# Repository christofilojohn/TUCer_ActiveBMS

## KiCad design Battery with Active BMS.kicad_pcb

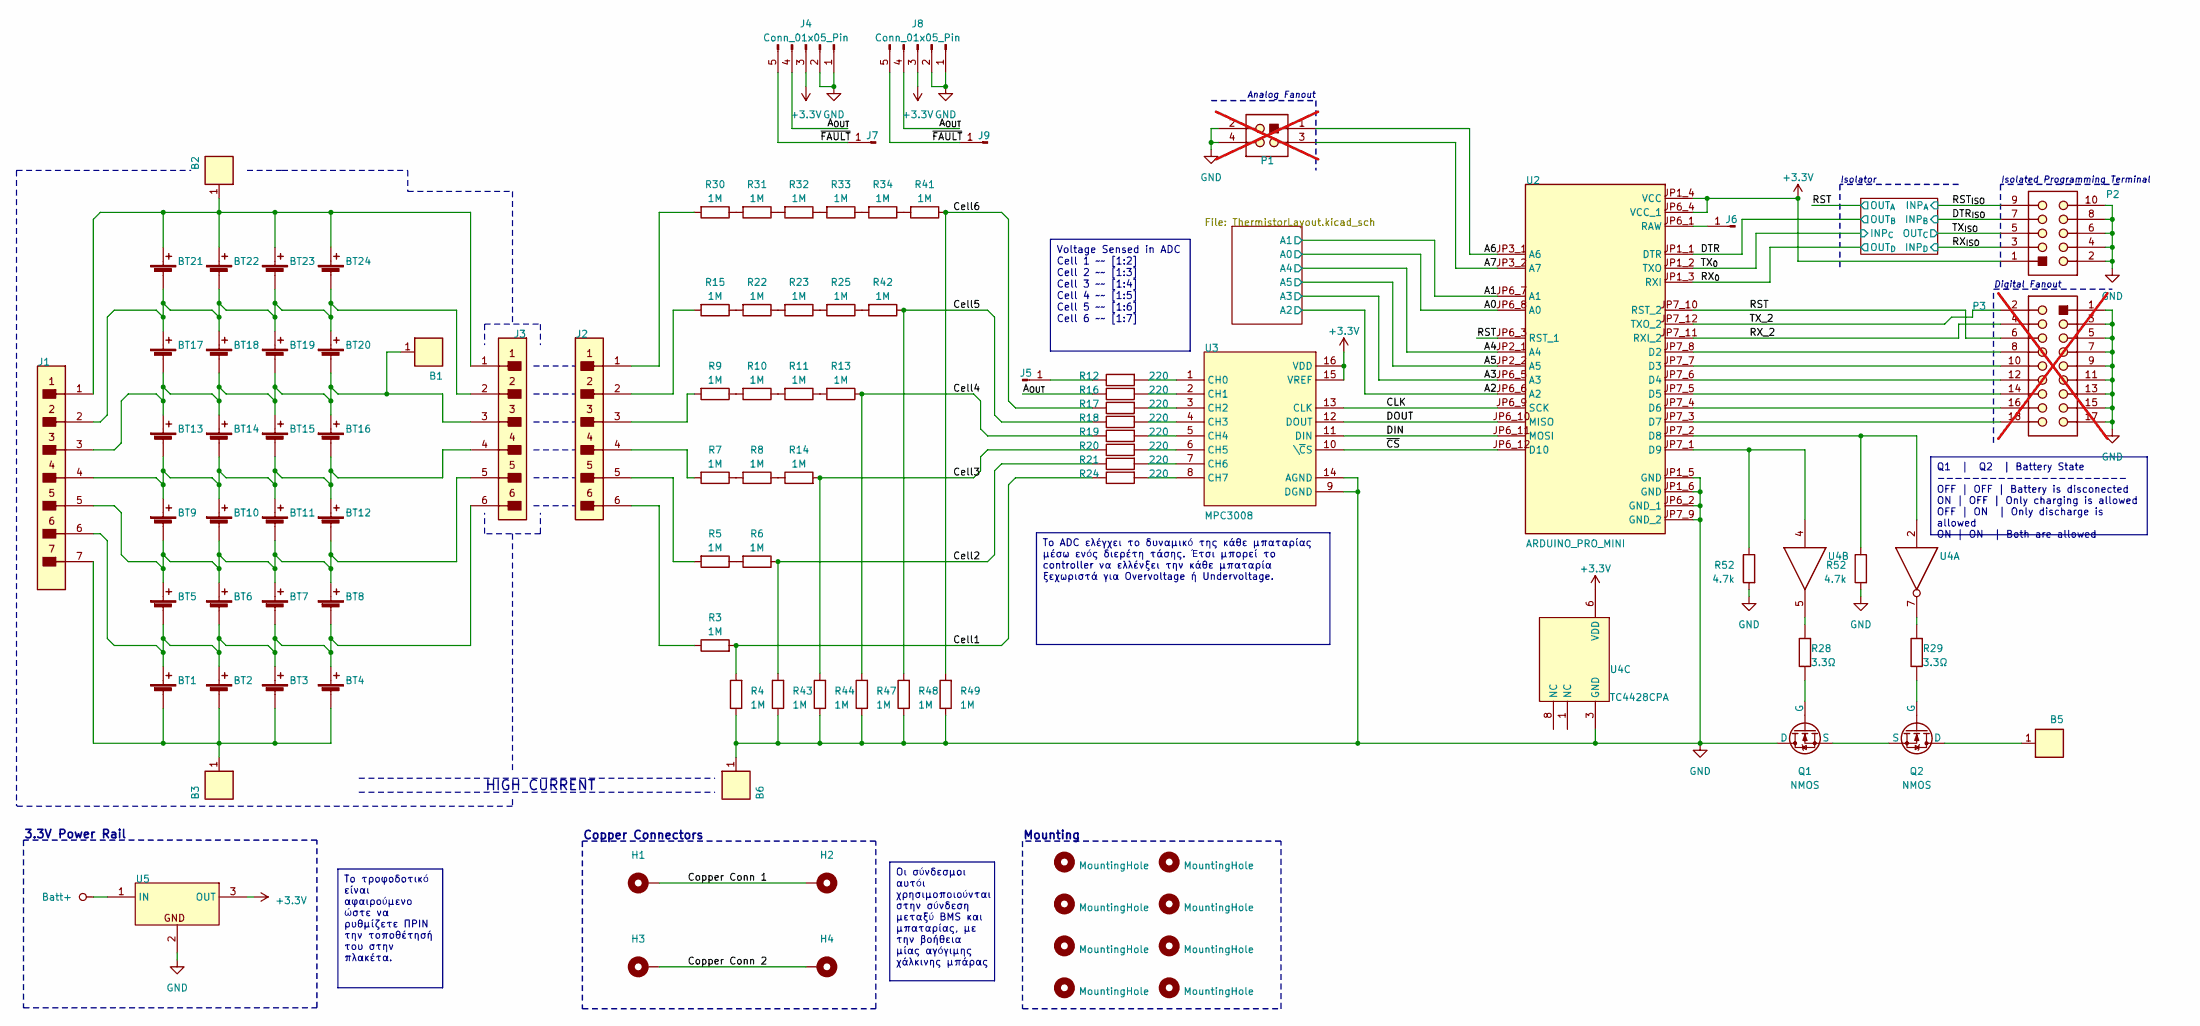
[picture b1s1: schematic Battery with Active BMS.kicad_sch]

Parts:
B1, B2, B3, B5, B6: 7461383; M5 Screw Terminal; MOUSER PART NUMBER 710-7461383
BT1, BT2, BT3, BT4, BT5, BT6, BT7, BT8, BT9, BT10, BT11, BT12, BT13, BT14, BT15, BT16, BT17, BT18, BT19, BT20, BT21, BT22, BT23, BT24: Battery_Cell; 21700
H1, H2, H3, H4: MountingHole_Pad; MountingHole_5.3mm_M5_Pad_Via
H5, H6, H7, H8, H9, H10, H11, H12: MountingHole; MountingHole_2.5mm_Pad
J1: B7B-EH-A(LF)(SN); JST_EH_B7B-EH-A_1x07_P2.50mm_Vertical; FLAMMABILITY RATING UL94 V-0; CURRENT RATING 3A
J2, J3: B7B-EH-A(LF)(SN); JST_EH_B6B-EH-A_1x06_P2.50mm_Vertical; FLAMMABILITY RATING UL94 V-0; CURRENT RATING 3A
J4, J8: Conn_01x05_Pin; PinSocket_1x05_P2.54mm_Vertical
J5, J6, J7, J9: Conn_01x01_Pin; PinSocket_1x01_P2.54mm_Vertical
P1: 22-28-4033; PinHeader_2x02_P2.54mm_Vertical; VOLTAGE RATING 250 V; CURRENT RATING 4 A; not fitted
P2: 61300511121; PinHeader_2x05_P2.54mm_Vertical; WORKING VOLTAGE 250VAC; WITHSTANDING VOLTAGE 500VAC; PART NUMBER 61300511121
P3: 61300811121; PinHeader_2x09_P2.54mm_Vertical; WORKING VOLTAGE 250VAC; WITHSTANDING VOLTAGE 500VAC; PART NUMBER 61300811121; not fitted
Q1, Q2: NMOS; IAUA250N04S6N005AUMA1
R3, R4, R5, R6, R7, R8, R9, R10, R11, R13, R14, R15, R22, R23, R25, R30, R31, R32, R33, R34, R41, R42, R43, R44, R47, R48, R49: 1M; R_Axial_DIN0207_L6.3mm_D2.5mm_P10.16mm_Horizontal
R12, R16, R17, R18, R19, R20, R21, R24, R28, R29: Res2; R_0805_2012Metric_Pad1.20x1.40mm_HandSolder
R52: 4.7k; R_0805_2012Metric_Pad1.20x1.40mm_HandSolder
U2: ARDUINO_PRO_MINI; MODULE_ARDUINO_PRO_MINI
U3: MPC3008; DIP-16_W7.62mm
U4: TC4428CPA; DIP-8_W7.62mm
U5: LM78M05CT/NOPB; PinSocket_1x03_P2.54mm_Vertical

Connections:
+3.3V: J4.3, J8.3, P2.1, U2.JP1_4 (VCC), U2.JP6_4 (VCC_1), U3.15 (VREF), U3.16 (VDD), U4.6 (VDD), U5.3 (OUT); also elsewhere on the board
/<NO NET>: P1.1, U2.JP3_1 (A6)
/A0: U2.JP6_8 (A0); also elsewhere on the board
/A1: U2.JP6_7 (A1); also elsewhere on the board
/A2: U2.JP6_6 (A2); also elsewhere on the board
/A3: U2.JP6_5 (A3); also elsewhere on the board
/A4: U2.JP2_1 (A4); also elsewhere on the board
/A5: U2.JP2_2 (A5); also elsewhere on the board
/A7: P1.3, U2.JP3_2 (A7)
/A_{OUT}: J4.4, J8.4, R16.1
/CLK: U2.JP6_9 (SCK), U3.13 (CLK)
/Cell1: R3.2, R4.2, R24.1
/Cell2: R6.1, R21.1, R43.2
/Cell3: R14.2, R20.1, R44.2
/Cell4: R13.1, R19.1, R47.2
/Cell5: R18.1, R42.1, R48.2
/Cell6: R17.1, R41.1, R49.2
/Copper Conn 1: H1.1, H2.1
/Copper Conn 2: H3.1, H4.1
/DIN: U2.JP6_11 (MOSI), U3.11 (DIN)
/DOUT: U2.JP6_10 (MISO), U3.12 (DOUT)
/DTR: U2.JP1_1 (DTR); also elsewhere on the board
/DTR_{ISO}: P2.7; also elsewhere on the board
/RST: P3.6, U2.JP6_3 (RST_1), U2.JP7_10 (RST_2); also elsewhere on the board
/RST_{ISO}: P2.9; also elsewhere on the board
/RX_2: P3.4, U2.JP7_11 (RXI_2)
/RX_{0}: U2.JP1_3 (RXI); also elsewhere on the board
/RX_{ISO}: P2.3; also elsewhere on the board
/TX_2: P3.2, U2.JP7_12 (TXO_2)
/TX_{0}: U2.JP1_2 (TXO); also elsewhere on the board
/~CS: U2.JP6_12 (D10), U3.10 (\~CS)
/~FAULT: J4.5, J7.1, J8.5, J9.1
Batt+: U5.1 (IN)
GND: B6.1, J4.1, J4.2, J8.1, J8.2, P1.2, P1.4, P2.2, P2.4, P2.6, P2.8, P2.10, P3.1, P3.3, P3.5, P3.7, P3.9, P3.11, P3.13, P3.15, P3.17, Q1.1 (D), R4.1, R43.1, R44.1, R47.1, R48.1, R49.1, R52.2, U2.JP1_5 (GND), U2.JP1_6 (GND), U2.JP6_2 (GND_1), U2.JP7_9 (GND_2), U3.9 (DGND), U3.14 (AGND), U4.3 (GND), U5.2 (GND); also elsewhere on the board
unnamed: BT1.1 (+), BT2.1 (+), BT3.1 (+), BT4.1 (+), BT5.2 (-), BT6.2 (-), BT7.2 (-), BT8.2 (-), J1.6, J3.6
unnamed: B3.1, BT1.2 (-), BT2.2 (-), BT3.2 (-), BT4.2 (-), J1.7
unnamed: BT9.1 (+), BT10.1 (+), BT11.1 (+), BT12.1 (+), BT13.2 (-), BT14.2 (-), BT15.2 (-), BT16.2 (-), J1.4, J3.4
unnamed: BT5.1 (+), BT6.1 (+), BT7.1 (+), BT8.1 (+), BT9.2 (-), BT10.2 (-), BT11.2 (-), BT12.2 (-), J1.5, J3.5
unnamed: B1.1, BT13.1 (+), BT14.1 (+), BT15.1 (+), BT16.1 (+), BT17.2 (-), BT18.2 (-), BT19.2 (-), BT20.2 (-), J1.3, J3.3
unnamed: BT17.1 (+), BT18.1 (+), BT19.1 (+), BT20.1 (+), BT21.2 (-), BT22.2 (-), BT23.2 (-), BT24.2 (-), J1.2, J3.2
unnamed: B2.1, BT21.1 (+), BT22.1 (+), BT23.1 (+), BT24.1 (+), J1.1, J3.1
unnamed: J2.1, R30.2
unnamed: J2.2, R15.2
unnamed: J2.3, R9.2
unnamed: J2.4, R7.2
unnamed: J2.5, R5.2
unnamed: J2.6, R3.1
unnamed: J5.1, R12.1
unnamed: J6.1, U2.JP6_1 (RAW)
unnamed: Q1.2 (G), R28.1
unnamed: Q1.3 (S), Q2.3 (S)
unnamed: B5.1, Q2.1 (D)
unnamed: Q2.2 (G), R29.1
unnamed: R5.1, R6.2
unnamed: R7.1, R8.2
unnamed: R10.1, R11.2
unnamed: R9.1, R10.2
unnamed: R11.1, R13.2
unnamed: R8.1, R14.1
unnamed: R15.1, R22.2
unnamed: R22.1, R23.2
unnamed: R23.1, R25.2
unnamed: R25.1, R42.2
unnamed: R30.1, R31.2
unnamed: R31.1, R32.2
unnamed: R32.1, R33.2
unnamed: R33.1, R34.2
unnamed: R34.1, R41.2
unnamed: P3.8, U2.JP7_8 (D2)
unnamed: P3.10, U2.JP7_7 (D3)
unnamed: P3.12, U2.JP7_6 (D4)
unnamed: P3.14, U2.JP7_5 (D5)
unnamed: P3.16, U2.JP7_4 (D6)
unnamed: P3.18, U2.JP7_3 (D7)
unnamed: R12.2, U3.1 (CH0)
unnamed: R16.2, U3.2 (CH1)
unnamed: R17.2, U3.3 (CH2)
unnamed: R18.2, U3.4 (CH3)
unnamed: R19.2, U3.5 (CH4)
unnamed: R20.2, U3.6 (CH5)
unnamed: R21.2, U3.7 (CH6)
unnamed: R24.2, U3.8 (CH7)
unnamed: R29.2, U4.7 (~OUTA)
unnamed: R28.2, U4.5 (OUTB)

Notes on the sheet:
Το τροφοδοτικό είναι αφαιρούμενο ώστε να ρυθμίζετε ΠΡΙΝ την τοποθέτησή του στην πλακέτα.
Voltage Sensed in ADC Cell 1 ~~ [1:2] Cell 2 ~~ [1:3] Cell 3 ~~ [1:4] Cell 4 ~~ [1:5] Cell 5 ~~ [1:6] Cell 6 ~~ [1:7]
Q1 | Q2 | Battery State ---------------------- OFF | OFF | Battery is disconected ON | OFF | Only charging is allowed OFF | ON | Only discharge is allowed ON | ON | Both are allowed
Το ADC ελέγχει το δυναμικό της κάθε μπαταρίας μέσω ενός διερέτη τάσης. Έτσι μπορεί το controller να ελλένξει την κάθε μπαταρία ξεχωριστά για Overvoltage ή Undervoltage.
Οι σύνδεσμοι αυτόι χρησιμοποιούνται στην σύνδεση μεταξύ BMS και μπαταρίας, με την βοήθεια μίας αγόγιμης χάλκινης μπάρας
Digital Fanout
3.3V Power Rail
HIGH CURRENT
Analog Fanout
Isolated Programming Terminal
Copper Connectors
Mounting
Isolator

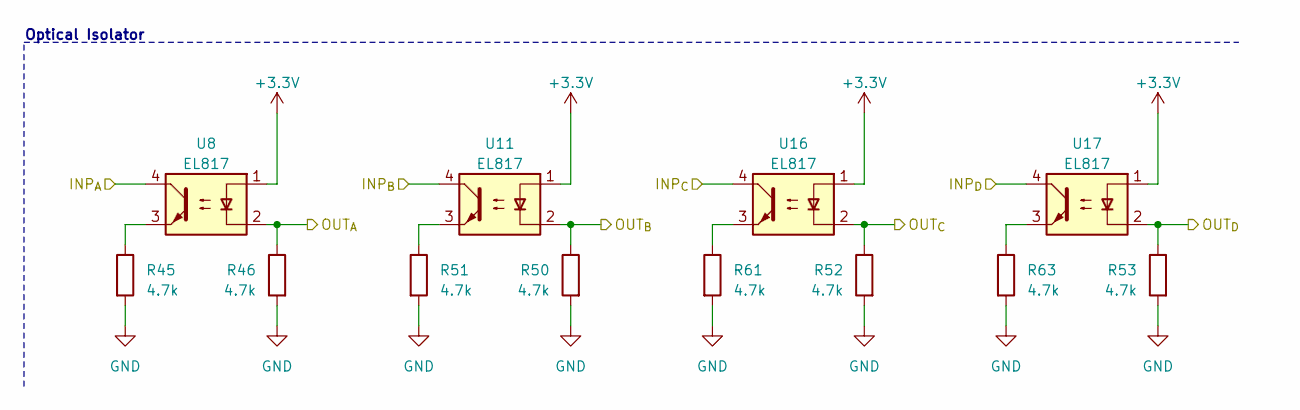
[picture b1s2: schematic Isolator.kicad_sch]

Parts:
R45, R46, R50, R51, R52, R53, R61, R63: 4.7k; R_0805_2012Metric_Pad1.20x1.40mm_HandSolder
U8, U11, U16, U17: EL817; DIP-4_W7.62mm

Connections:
+3.3V: U8.1, U11.1, U16.1, U17.1; also elsewhere on the board
/DTR: R50.1, U11.2; also elsewhere on the board
/DTR_{ISO}: U11.4; also elsewhere on the board
/RST: R46.1, U8.2; also elsewhere on the board
/RST_{ISO}: U8.4; also elsewhere on the board
/RX_{0}: R53.1, U17.2; also elsewhere on the board
/RX_{ISO}: U17.4; also elsewhere on the board
/TX_{0}: U16.4; also elsewhere on the board
GND: R45.2, R46.2, R50.2, R51.2, R52.2, R53.2, R61.2, R63.2; also elsewhere on the board
unnamed: R45.1, U8.3
unnamed: R51.1, U11.3
unnamed: R61.1, U16.3
unnamed: R63.1, U17.3

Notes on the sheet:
Optical Isolator

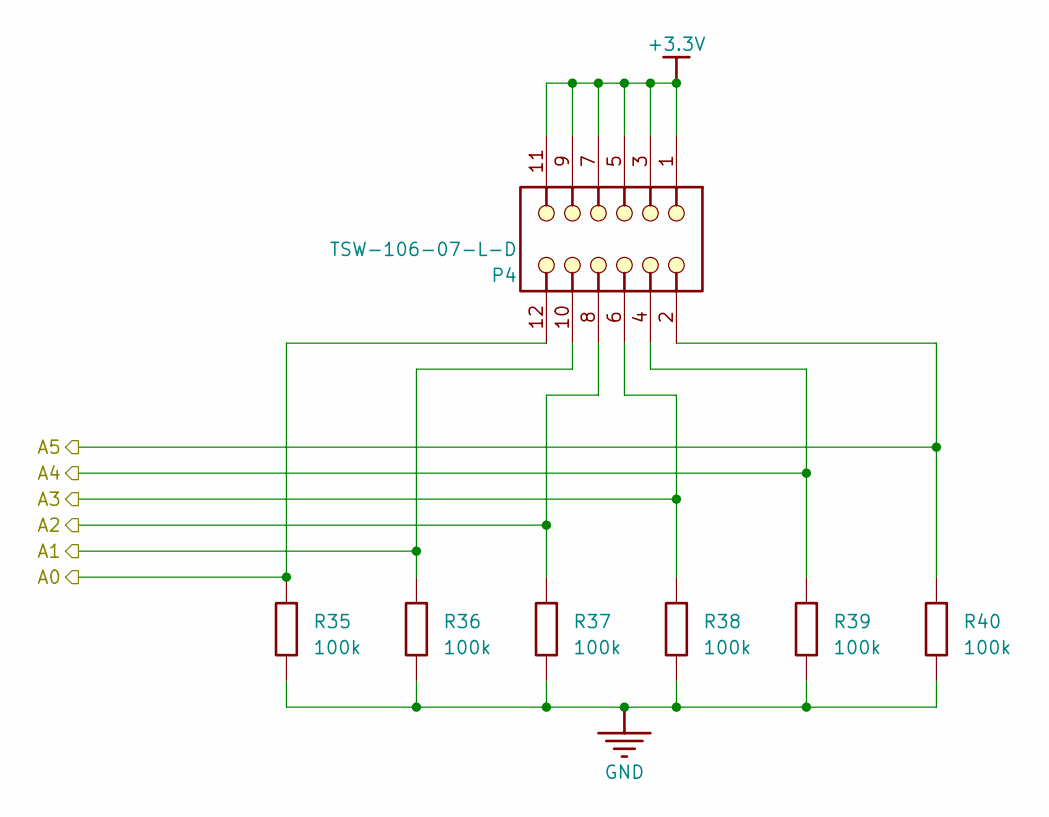
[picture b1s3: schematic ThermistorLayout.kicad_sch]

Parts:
P4: TSW-106-07-L-D; PinHeader_2x06_P2.54mm_Vertical; PARTNUMBER TSW-106-07-L-D
R35, R36, R37, R38, R39, R40: Res2; R_0805_2012Metric_Pad1.20x1.40mm_HandSolder

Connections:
+3.3V: P4.1, P4.3, P4.5, P4.7, P4.9, P4.11; also elsewhere on the board
/A0: P4.12, R35.2; also elsewhere on the board
/A1: P4.10, R36.2; also elsewhere on the board
/A2: P4.8, R37.2; also elsewhere on the board
/A3: P4.6, R38.2; also elsewhere on the board
/A4: P4.4, R39.2; also elsewhere on the board
/A5: P4.2, R40.2; also elsewhere on the board
GND: R35.1, R36.1, R37.1, R38.1, R39.1, R40.1; also elsewhere on the board

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
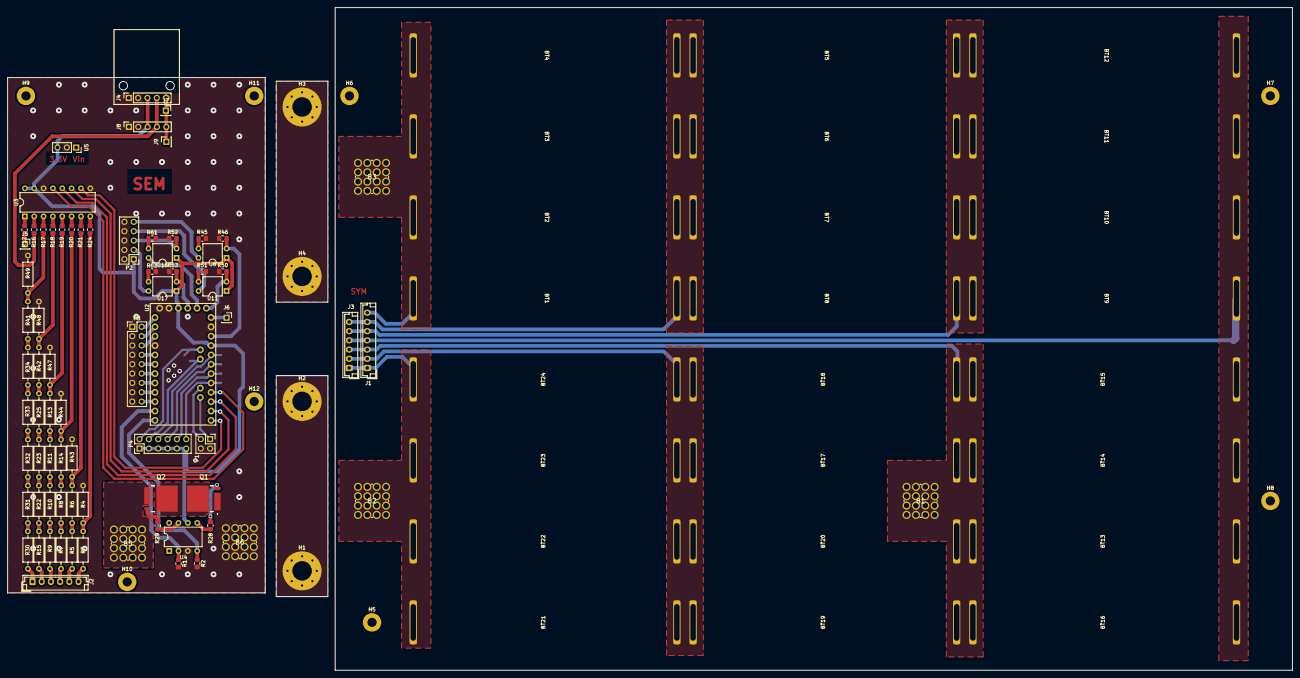
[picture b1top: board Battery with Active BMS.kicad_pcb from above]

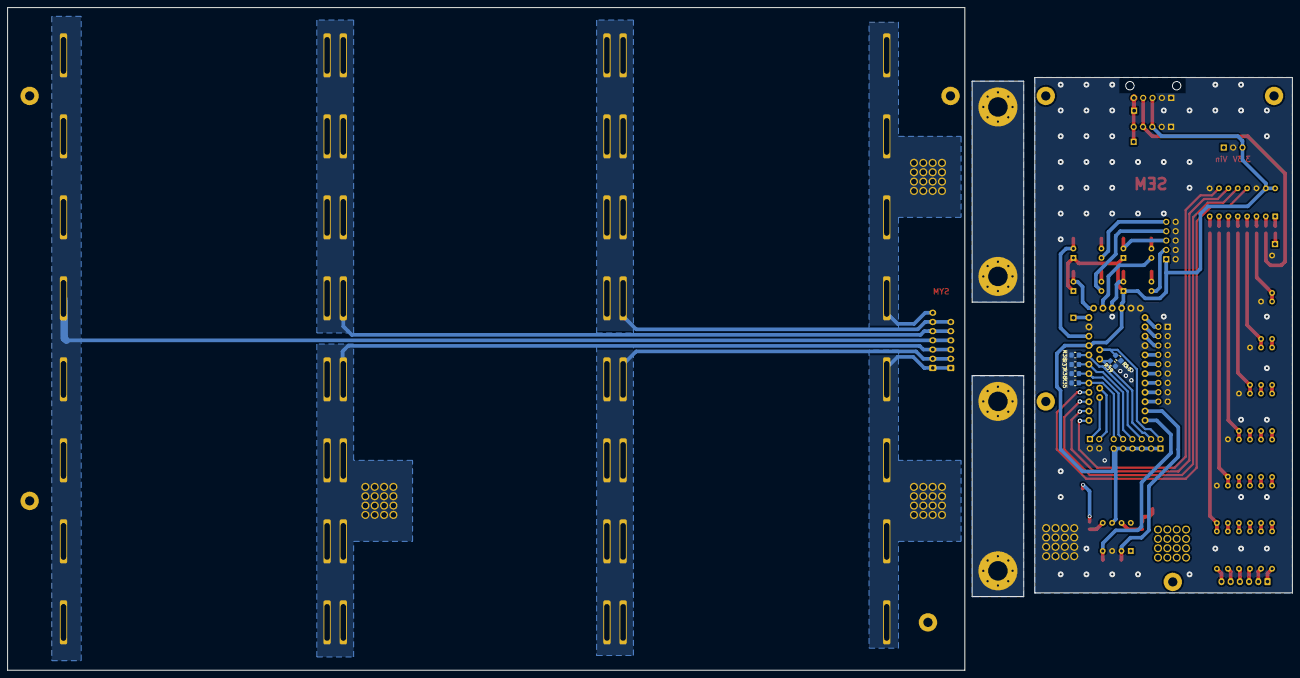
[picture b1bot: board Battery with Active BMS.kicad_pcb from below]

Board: 2 copper layers, 349.0 x 180.0 mm, 117 parts (6 on the bottom side), 90 nets.

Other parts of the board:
R1, R2: 4.7k; R_0805_2012Metric_Pad1.20x1.40mm_HandSolder

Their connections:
GND: R1.2, R2.2; also elsewhere on the board

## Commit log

2023-04-30 Initial Upload - Move workspace to cloud
2023-04-30 V0.1 Upload
2023-05-02 BMS V1.0
2023-05-11 Battery Managment System V1.0
2023-05-20 Added BMS controller
    Wrote a BMS controller based on the specifications of our autonomous vehicle
